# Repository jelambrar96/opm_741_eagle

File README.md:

# Amplificador operacional 741 

Recreación del circuito interno del amplificador operacional 741 construido
a partir de transistores **2N3906**, **2N3904** y resistencias. 

## Original

## Board

## Schematic

## Componentes usados: 
- 11 Transistores NPN 2n3914
- 7 Transistores PNP 2n3906
- Resitencias:
    - 2 Resistencias de 50 KOhm 
    - 1 Resistencia de 39 KOhm
    - 2 Resistencias de 10 KOhm
    - 1 Resistencia de 5 KOhm
    - 1 Resistencia de 4.5 KOhm
    - 2 Resistencias de 1 KOhm
    - 2 Resistencias de 50 Ohm
    - 1 Resistencia de 25 Ohm
- capacitor cerámico 39uF
- Potenciómetro 10 kOhm

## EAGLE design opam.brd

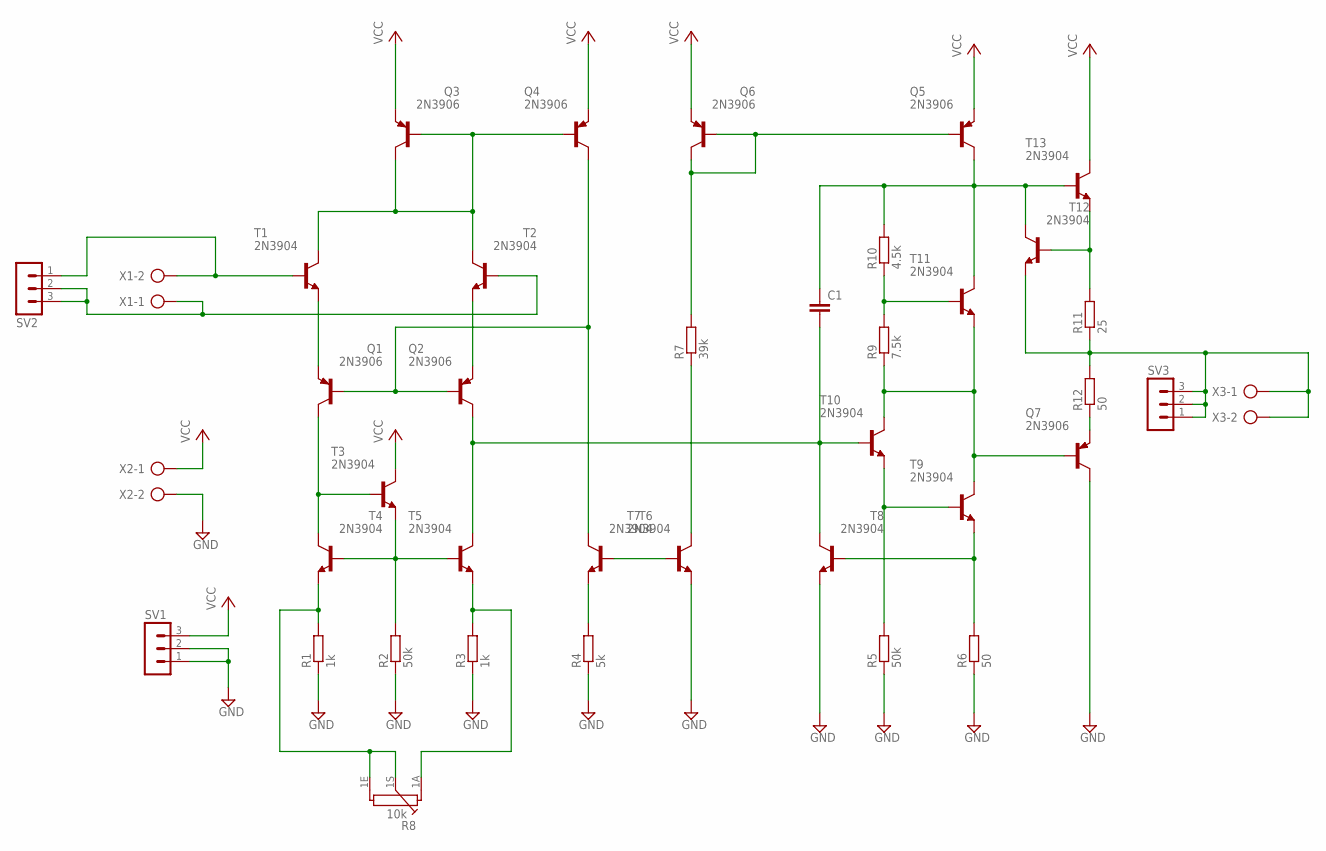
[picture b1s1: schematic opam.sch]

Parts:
C1: C2.5/5; C2.5-5
Q1, Q2, Q3, Q4, Q5, Q6, Q7: 2N3906; TO92
R1, R3: 1k; 0309/12
R2, R5: 50k; 0309/12
R4: 5k; 0309/12
R6, R12: 50; 0309/12
R7: 39k; 0309/12
R8: 10k; PC16S
R9: 7.5k; 0309/12
R10: 4.5k; 0309/12
R11: 25; 0309/12
SV1, SV2, SV3: MA03-1
T1, T2, T3, T4, T5, T6, T7, T8, T9, T10, T11, T12, T13: 2N3904; TO92
X1, X2, X3: AK500/2-H

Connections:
GND: Q7.1 (C), R1.1, R2.1, R3.1, R4.1, R5.1, R6.1, SV1.1, SV1.2, T7.3 (E), T8.3 (E), X2.2
unnamed: R5.2, T9.2 (B), T10.3 (E)
unnamed: R2.2, T3.3 (E), T4.2 (B), T5.2 (B)
unnamed: R3.2, R8.1A, T5.3 (E)
unnamed: SV2.1, T1.2 (B), X1.2
unnamed: Q1.1 (C), T3.2 (B), T4.1 (C)
unnamed: Q1.3 (E), T1.3 (E)
unnamed: Q2.3 (E), T2.3 (E)
unnamed: Q1.2 (B), Q2.2 (B), Q4.1 (C), T6.1 (C)
unnamed: Q3.1 (C), Q3.2 (B), Q4.2 (B), T1.1 (C), T2.1 (C)
unnamed: R6.2, T8.2 (B), T9.3 (E)
unnamed: R1.2, R8.1E, R8.1S, T4.3 (E)
unnamed: Q7.3 (E), R12.1
unnamed: R4.2, T6.3 (E)
unnamed: T6.2 (B), T7.2 (B)
unnamed: R7.1, T7.1 (C)
unnamed: Q5.2 (B), Q6.1 (C), Q6.2 (B), R7.2
unnamed: C1.2, Q2.1 (C), T5.1 (C), T8.1 (C), T10.2 (B)
unnamed: Q7.2 (B), R9.1, T9.1 (C), T10.1 (C), T11.3 (E)
unnamed: C1.1, Q5.1 (C), R10.2, T11.1 (C), T12.1 (C), T13.2 (B)
unnamed: R11.2, T12.2 (B), T13.3 (E)
unnamed: R9.2, R10.1, T11.2 (B)
unnamed: SV2.2, SV2.3, T2.2 (B), X1.1
unnamed: R11.1, R12.2, SV3.1, SV3.2, SV3.3, T12.3 (E), X3.1, X3.2
VCC: Q3.3 (E), Q4.3 (E), Q5.3 (E), Q6.3 (E), SV1.3, T3.1 (C), T13.1 (C), X2.1

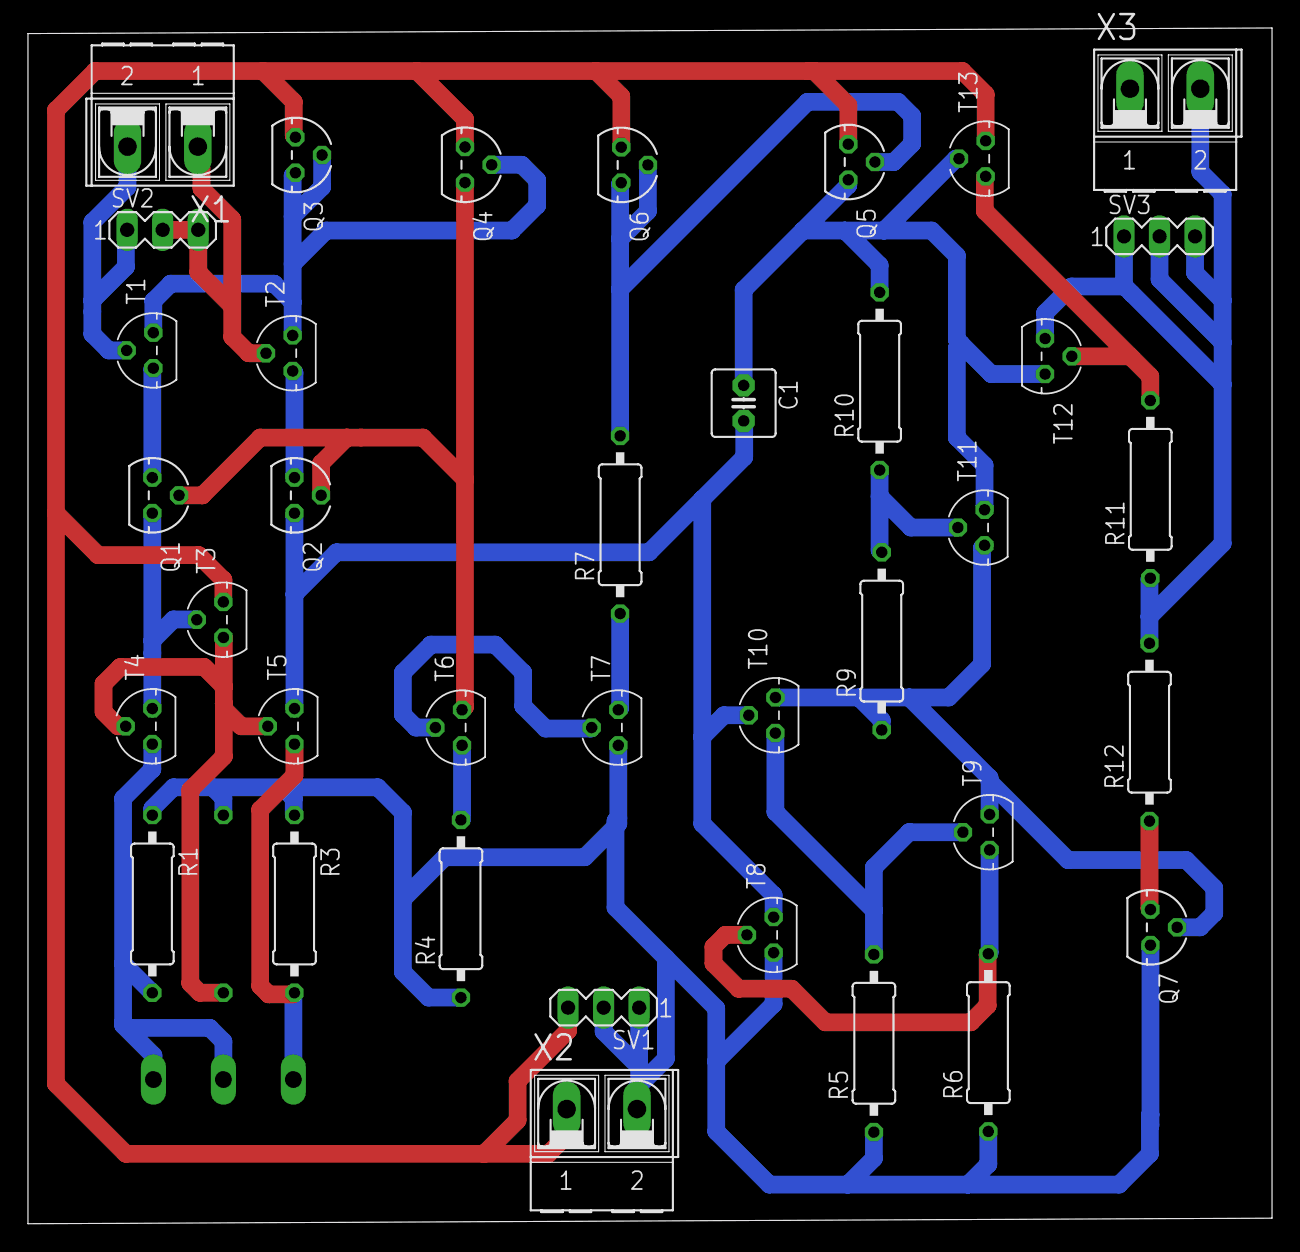
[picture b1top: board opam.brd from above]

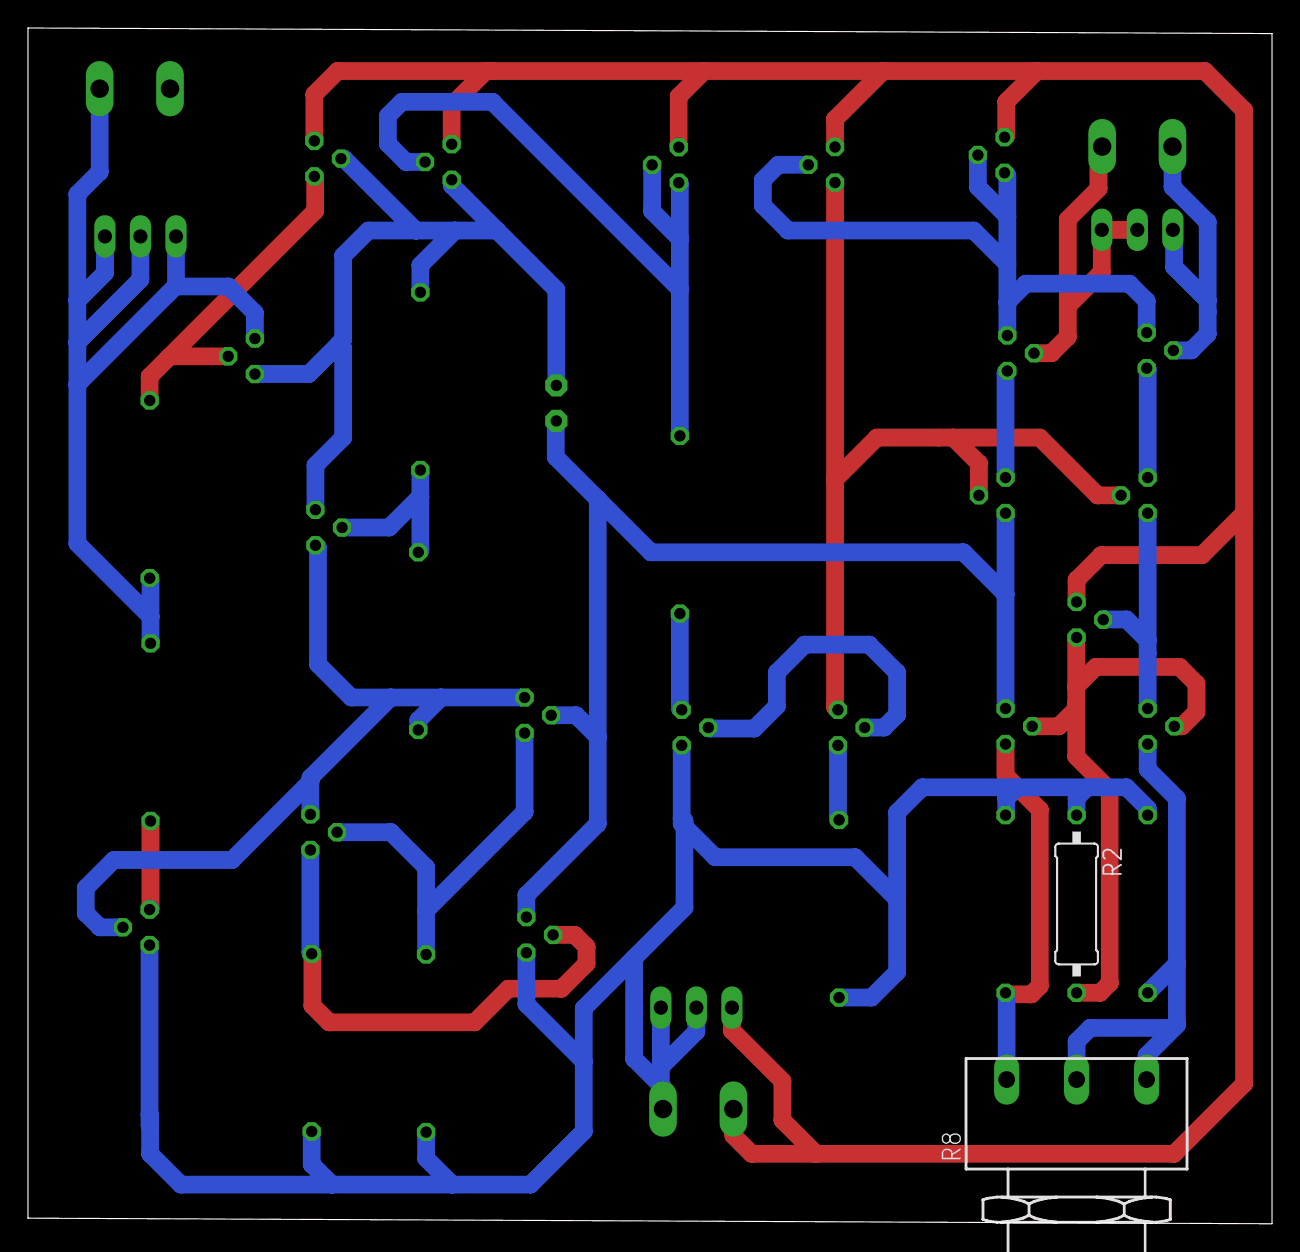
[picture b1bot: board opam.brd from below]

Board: 2 copper layers, 88.9 x 85.5 mm, 39 parts (2 on the bottom side), 25 nets.

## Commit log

2019-04-19 git .gitignore
2019-04-19 add some files
2019-04-19 add images
